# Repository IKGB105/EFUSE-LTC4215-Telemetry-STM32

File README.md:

# Hot-Swap eFuse Telemetry (LTC4215 + STM32F411CEU6)

Digital telemetry front-end for the [EFUSE-LTC4215-HotSwap](https://github.com/IKGB105/EFUSE-LTC4215-HotSwap)
board: adds a minimal STM32F411CEU6 system wired to the LTC4215's I²C/SMBus monitoring interface,
which the original design left completely unused. Same honest-engineering-logbook documentation
style as the rest of the series — every result marked calculated, simulated, or pending, no invented
placeholders.

- **Why:** the LTC4215 has an onboard ADC and I²C register map for current/voltage/fault monitoring
  that the original eFuse project never touched. This project closes that gap instead of starting an
  unrelated MCU exercise.
- **MCU:** STM32F411CEU6 (same part as the WeAct "Blackpill"), chosen for native USB-DFU flashing and
  headroom for future command parsing — not just familiarity.
- **Scope:** schematic + PCB layout only, same convention as every project in this series. Not
  physically built.

> ⚠️ **The LTC4215 is not PMBus-compliant.** It has its own proprietary I²C register map, not the
> standardized PMBus command set — described here as "digital power monitoring in the spirit of
> PMBus," not as a PMBus device, to avoid overstating the IC.

<table>
<tr>
<td><br><sub>KiCad — schematic</sub></td>
<td><br><sub>KiCad — PCB 3D render</sub></td>
<td><br><sub>KiCad — top copper routing</sub></td>
</tr>
</table>

## I²C integration with the LTC4215

The original eFuse board left every I²C-related pin (SCL, SDAI, SDAO, ADR0-2) no-connect. This
revision wires them per the datasheet:

- **SDAI + SDAO tied together** to form the bidirectional SDA line (the QFN exposes them separately
  only to allow an optoisolator on SDAO alone — not used here).
- **Address set to 19** (`ADR2`/`ADR0` to INTVCC, `ADR1` floating) — reproduced from the datasheet's
  own worked example (Figure 5), not an arbitrary value, since it's the only device on the bus.
- **Pull-ups referenced to INTVCC** (≈3.1 V typ, confirmed from the datasheet's electrical table to
  be close enough to 3.3 V logic that no level shifter is needed): 4.7 kΩ on SCL/SDA, 10 kΩ on ALERT.
- **-ALERT**, previously unused, now routed to the STM32 as an EXTI interrupt source.

## STM32 minimal system

Built from the real WeAct Blackpill reference schematic (`docs/reference/`), kept where it was
correct and corrected where it was not — see the report's pitfalls section for specifics:

- 3× VDD + 4× VSS (the UFQFPN48's exposed pad is a 4th, hidden VSS pin stacked on the visible one —
  verified directly from the symbol library file, not assumed).
- VCAP1 (2.2 µF, required for the F4's internal core regulator) and a VDDA/VREF+ LC filter.
- 25 MHz/9 pF crystal, 12 pF loading caps — **no RTC crystal/battery**, intentionally dropped (not
  needed for I²C telemetry).
- BOOT0 **and BOOT1** (shared with PB2 on the F401/F410/F411/F412 value line) pull-downs — confirmed
  against RM0383 §2.4 that BOOT1 is real on this part, not an F1-series leftover as first assumed.
- USB-C with a properly impedance-controlled D+/D− differential pair (90.2 Ω, computed from this
  board's real 2-layer stackup, not a generic assumption) and independent CC1/CC2 pull-downs.
- Single-stage **12 V → 3.3 V** LDO (LD1117S33TR) direct from the eFuse's +12 V rail — not the real
  Blackpill's two-stage USB-fed supply, since this board is never USB-powered.

## Firmware

I²C driver for the LTC4215 (`code/EFUSE_TELEMETRY/Core/{Inc,Src}/ltc4215.c,h`), on a STM32CubeMX
skeleton (I2C1 on PB6/PB7, USB\_OTG\_FS device-only with VBUS sensing disabled, USB\_DEVICE as
CDC/Virtual COM Port). Register map (CONTROL/ALERT/STATUS/FAULT/SENSE/SOURCE/ADIN, 00h-06h) and LSB
values taken straight from the datasheet's Tables 2-8, not re-derived. Main loop polls every 500 ms
and streams output current/voltage/fault flags over USB-CDC.

**Verified without any physical board, two ways:**
- Compiles clean against the real HAL — CMake + `arm-none-eabi-gcc`, 0 errors/warnings, 36020 B FLASH
  (6.87%), 9456 B RAM (7.21%).
- The register-to-physical-value math is checked on the **host** (plain `gcc`, no STM32 hardware) in
  [`code/test/ltc4215_regmap_test.c`](code/test/ltc4215_regmap_test.c) against synthetic bytes derived
  from the datasheet's LSB values — 11/11 checks pass.

Neither claims real I²C traffic with a physical LTC4215 — this board was never built.

## Repository structure

```
docs/         LaTeX report (efuse_telemetry_stm32.tex) + datasheet + WeAct reference schematic
kicad/        KiCad project — schematic + PCB, ERC/DRC clean
code/         STM32CubeMX project (CMake) + LTC4215 driver + host-side unit test
```

## Document

The full report (MCU selection rationale, I²C integration design, STM32 minimal-system design, PCB
layout decisions, and every pitfall found along the way — net-name collisions, hidden/stacked pins,
4-pad crystal footprints, differential pair impedance synthesis, a confirmed BOOT1 requirement) is in
[`docs/efuse_telemetry_stm32.pdf`](docs/efuse_telemetry_stm32.pdf) — compiled and committed. Source
is [`docs/efuse_telemetry_stm32.tex`](docs/efuse_telemetry_stm32.tex) if you want to edit or
recompile it yourself (`pdflatex`).

## PCB (KiCad)

In [`kicad/EFUSE_TELEMETRY/`](kicad/EFUSE_TELEMETRY/) — ERC and DRC both clean (the only remaining
DRC entries are inherent to the USB-C connector footprint itself: hole clearance to its own mounting
holes, and the four intentionally-No-Connect VBUS pads touching each other). Single sheet, organized
into labeled blocks (Controller, Protection, Power, Connectors, STM32 Microprocessor, MCU Support,
STM32 Decoupling, USB-C, 12V→3.3V) rather than hierarchical sheets — the board is small enough that
visual grouping is clearer.

## PDN analysis

<br>
<sub>padne — DC voltage distribution: 12V eFuse input (yellow/red) and the 3.3V/GND plane under the
STM32's 50mA load (purple), at most 148µV of drop.</sub>

DC voltage-drop check done with [`padne`](https://github.com/atx/padne) (built from source — needs
`boost` dev headers for its CGAL dependency): under the STM32's estimated 50 mA load, the 3.3 V/GND
plane shows at most **148 µV** of drop — the copper is far from the bottleneck at this current level.
`!padne` directives live as plain text in the schematic, not the PCB. Full write-up (including the
`REGULATOR`+`CURRENT` solver interaction that made the LDO need modeling as a plain ideal source
instead) in the report.

AC impedance-vs-frequency sweep (the actual question for a digital decoupling bank — DC drop is blind
to capacitors entirely) is planned with [KiPI](https://github.com/drewsum/KiPI) — installed and
loading the board, but the probe/sweep setup wasn't finished this session.

## License

MIT — see [LICENSE](LICENSE).

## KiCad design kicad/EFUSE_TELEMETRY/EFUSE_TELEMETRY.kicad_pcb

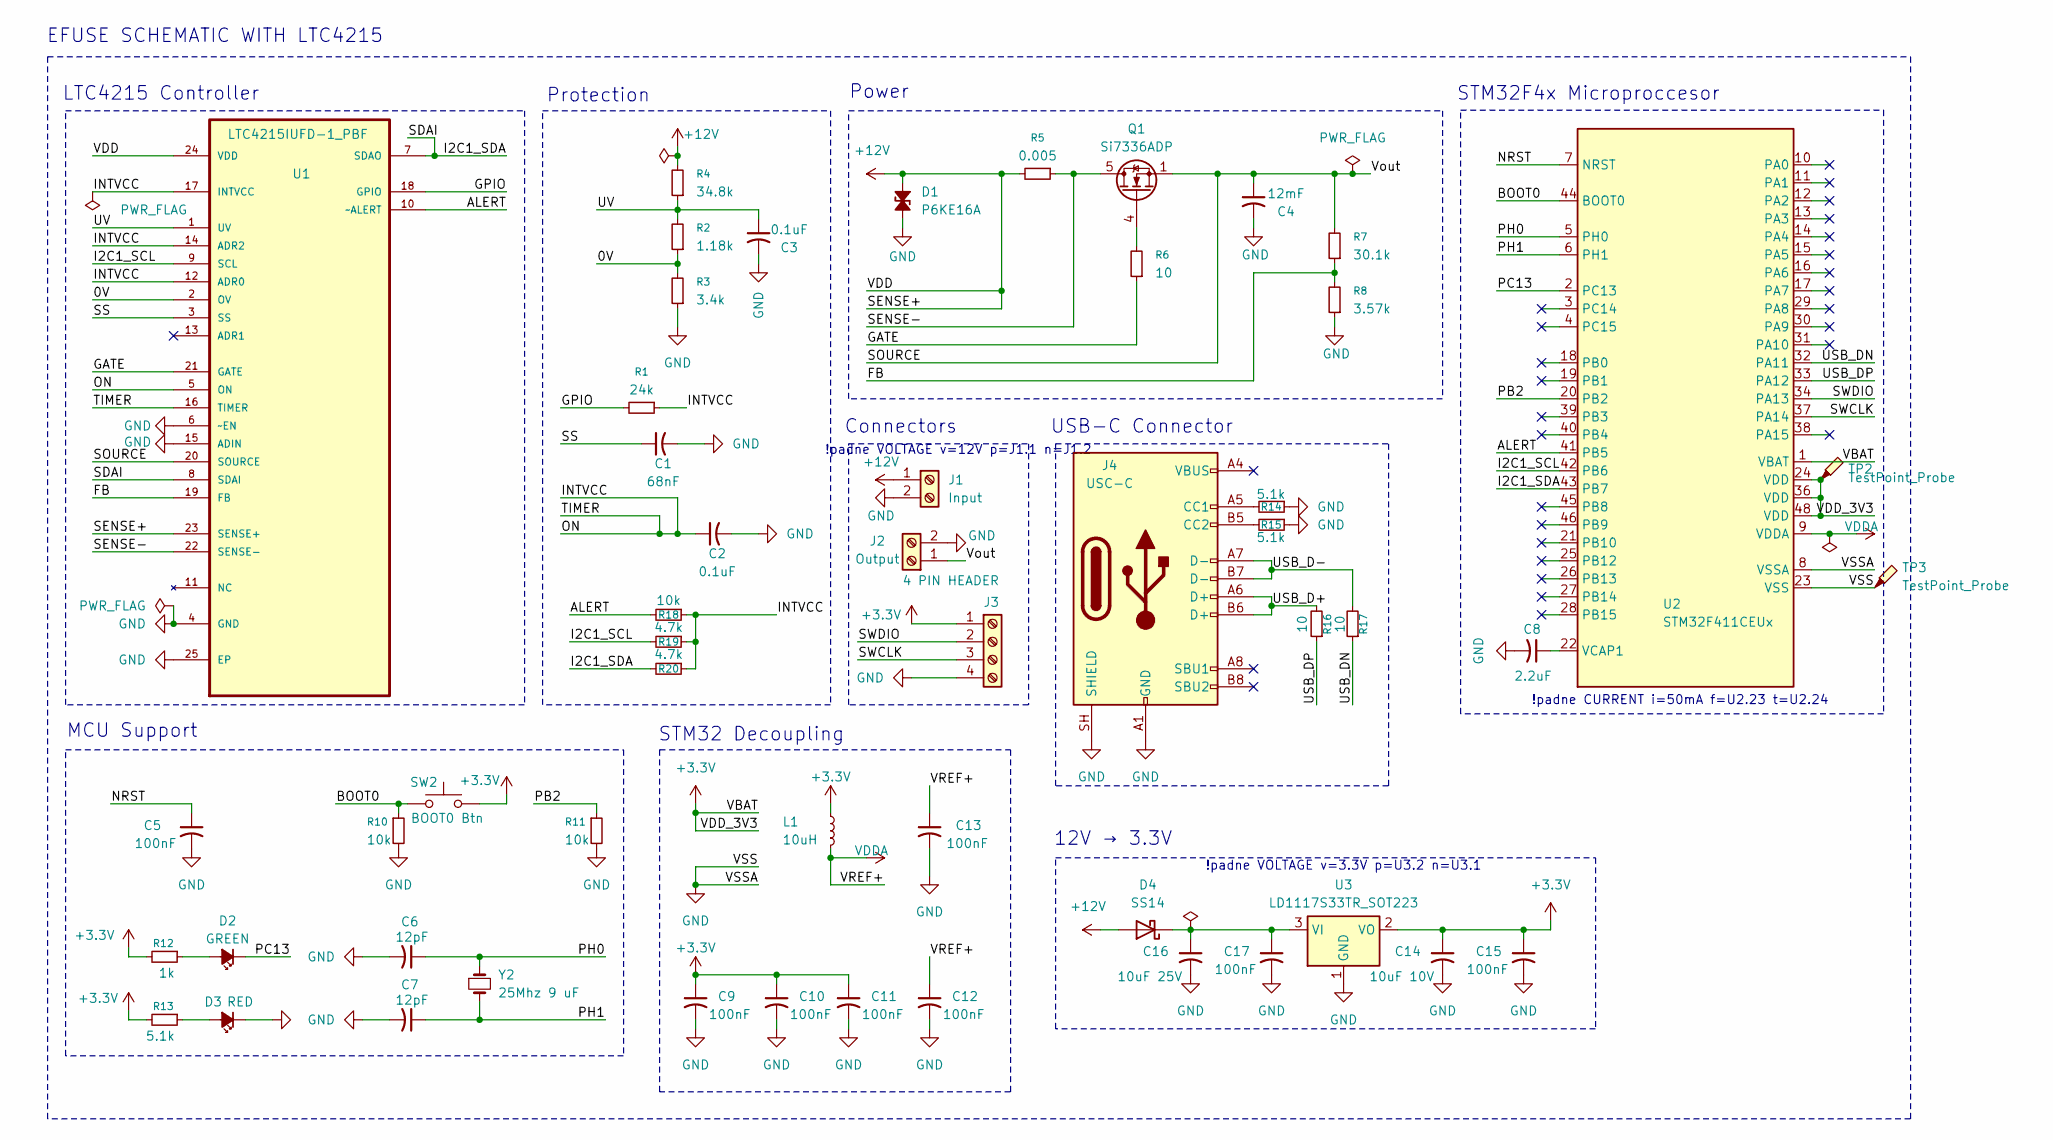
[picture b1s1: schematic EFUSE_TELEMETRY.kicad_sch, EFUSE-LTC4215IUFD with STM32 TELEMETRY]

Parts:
C1: 68nF; C_0805_2012Metric
C2, C3: 0.1uF; C_0805_2012Metric
C4: 12mF; CP_Radial_D16.0mm_P7.50mm
C5, C9, C10, C11, C12, C13, C15, C17: 100nF; C_0805_2012Metric
C6, C7: 12pF; C_0201_0603Metric
C8: 2.2uF; C_0805_2012Metric
C14: 10uF 10V; C_1206_3216Metric
C16: 10uF 25V; C_1206_3216Metric
D1: P6KE16A; D_DO-15_P10.16mm_Horizontal
D2: GREEN; LED_0603_1608Metric
D3: RED; LED_0603_1608Metric
D4: SS14; D_SMA
J1: Input; AMASS_XT60-M_1x02_P7.20mm_Vertical
J2: Output; AMASS_XT60-M_1x02_P7.20mm_Vertical
J3: 4 PIN HEADER; PinHeader_1x04_P2.54mm_Vertical
J4: USC-C; USB_C_Receptacle_GCT_USB4105-xx-A_16P_TopMnt_Horizontal
L1: 10uH; L_0805_2012Metric
Q1: Si7336ADP; PowerPAK_SO-8_Single
R1: 24k; R_0805_2012Metric
R2: 1.18k; R_0805_2012Metric
R3: 3.4k; R_0805_2012Metric
R4: 34.8k; R_0805_2012Metric
R5: 0.005; R_2512_6332Metric
R6, R16, R17: 10; R_0805_2012Metric
R7: 30.1k; R_0805_2012Metric
R8: 3.57k; R_0805_2012Metric
R10, R11, R18: 10k; R_0805_2012Metric
R12: 1k; R_0805_2012Metric
R13, R14, R15: 5.1k; R_0805_2012Metric
R19, R20: 4.7k; R_0805_2012Metric
SW2: BOOT0 Btn; SW_Tactile_SPST_NO_Straight_CK_PTS636Sx25SMTRLFS
TP2, TP3: TestPoint_Probe; TestPoint_Keystone_5000-5004_Miniature
U1: LTC4215IUFD-1_PBF; QFN50P400X500X80-25N; MPN LTC4215IUFD-2#TRPBF; DigiKey_Part_Number LTC4215IUFD-1#PBF-ND
U2: STM32F411CEUx; QFN-48-1EP_7x7mm_P0.5mm_EP5.6x5.6mm
U3: LD1117S33TR_SOT223; SOT-223-3_TabPin2
Y2: 25Mhz 9 uF; Crystal_SMD_3225-4Pin_3.2x2.5mm

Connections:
+3.3V: C9.1, C10.1, C11.1, C14.1, C15.1, J3.1, L1.1, R12.2, R13.2, SW2.2, TP2.1 (1_1), U2.1 (VBAT), U2.24 (VDD), U2.36 (VDD), U2.48 (VDD), U3.2 (VO)
+12V: D1.1 (A1), D4.2 (A), J1.1, R4.2, R5.2, U1.23 (SENSE+), U1.24 (VDD)
/0V: R2.1, R3.2, U1.2 (OV)
/ALERT: R18.2, U1.10 (~ALERT), U2.41 (PB5)
/BOOT0: R10.1, SW2.1, U2.44 (BOOT0)
/FB: R7.1, R8.2, U1.19 (FB)
/GATE: R6.1, U1.21 (GATE)
/GPIO: R1.2, U1.18 (GPIO)
/I2C1_SCL: R19.2, U1.9 (SCL), U2.42 (PB6)
/I2C1_SDA: R20.2, U1.7 (SDAO), U1.8 (SDAI), U2.43 (PB7)
/INTVCC: C2.1, R1.1, R18.1, R19.1, R20.1, U1.5 (ON), U1.12 (ADR0), U1.14 (ADR2), U1.16 (TIMER), U1.17 (INTVCC)
/NRST: C5.1, U2.7 (NRST)
/PB2: R11.1, U2.20 (PB2)
/PC13: D2.1 (K), U2.2 (PC13)
/PH0: C6.1, U2.5 (PH0), Y2.1
/PH1: C7.1, U2.6 (PH1), Y2.2
/SENSE-: Q1.5 (D), R5.1, U1.22 (SENSE-)
/SOURCE: C4.1, J2.1, Q1.1 (S), Q1.2 (S), Q1.3 (S), R7.2, U1.20 (SOURCE)
/SS: C1.1, U1.3 (SS)
/SWCLK: J3.3, U2.37 (PA14)
/SWDIO: J3.2, U2.34 (PA13)
/USB_D+: J4.A6 (D+), J4.B6 (D+), R16.2
/USB_D-: J4.A7 (D-), J4.B7 (D-), R17.2
/USB_DN: R17.1, U2.32 (PA11)
/USB_DP: R16.1, U2.33 (PA12)
/UV: C3.1, R2.2, R4.1, U1.1 (UV)
GND: C1.2, C2.2, C3.2, C4.2, C5.2, C6.2, C7.2, C8.2, C9.2, C10.2, C11.2, C12.2, C13.2, C14.2, C15.2, C16.2, C17.2, D1.2 (A2), D3.1 (K), J1.2, J2.2, J3.4, J4.A1 (GND), J4.A12 (GND), J4.B1 (GND), J4.B12 (GND), J4.SH (SHIELD), R3.1, R8.1, R10.2, R11.2, R14.1, R15.1, TP3.1 (1_1), U1.4 (GND), U1.6 (~EN), U1.15 (ADIN), U1.25 (EP), U2.8 (VSSA), U2.23 (VSS), U2.35 (VSS), U2.47 (VSS), U2.49 (VSS), U3.1 (GND)
unnamed: D2.2 (A), R12.1
unnamed: D3.2 (A), R13.1
unnamed: C16.1, C17.1, D4.1 (K), U3.3 (VI)
unnamed: J4.A5 (CC1), R14.2
unnamed: J4.B5 (CC2), R15.2
unnamed: Q1.4 (G), R6.2
unnamed: C8.1, U2.22 (VCAP1)
VDDA: C12.1, C13.1, L1.2, U2.9 (VDDA)

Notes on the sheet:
STM32F4x Microproccesor
Power
!padne CURRENT i=50mA f=U2.23 t=U2.24
MCU Support
STM32 Decoupling
!padne VOLTAGE v=3.3V p=U3.2 n=U3.1
Connectors
!padne VOLTAGE v=12V p=J1.1 n=J1.2
Protection
12V → 3.3V
LTC4215 Controller
EFUSE SCHEMATIC WITH LTC4215
USB-C Connector

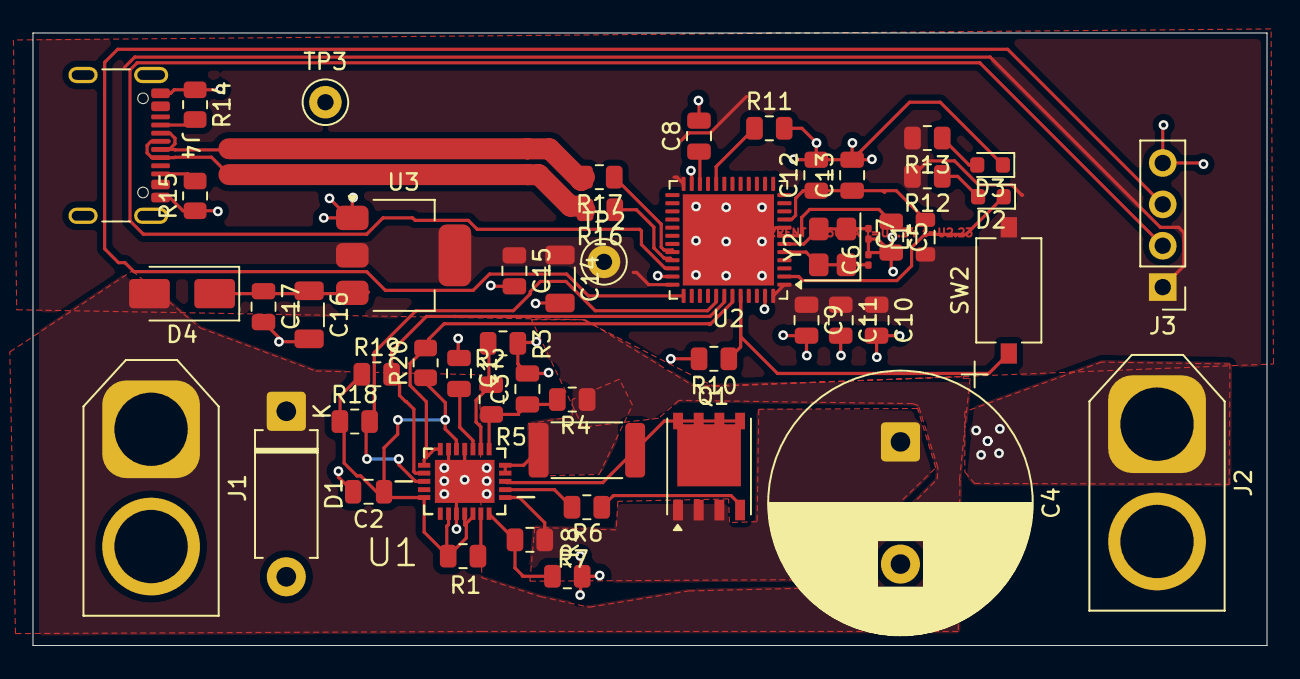
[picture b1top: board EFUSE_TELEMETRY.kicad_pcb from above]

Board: 2 copper layers, 75.8 x 37.6 mm, 53 parts (0 on the bottom side), 35 nets.

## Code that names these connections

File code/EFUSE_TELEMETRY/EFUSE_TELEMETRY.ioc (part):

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Mcu.Name=STM32F411C(C-E)Ux
Mcu.Package=UFQFPN48
Mcu.UserName=STM32F411CEUx
PA11.Mode=Device_Only
PA11.Signal=USB_OTG_FS_DM
PA12.Mode=Device_Only
PA12.Signal=USB_OTG_FS_DP
PB6.Mode=I2C
PB6.Signal=I2C1_SCL
PB7.Mode=I2C
PB7.Signal=I2C1_SDA
PH0\ -\ OSC_IN.Mode=HSE-External-Oscillator
PH0\ -\ OSC_IN.Signal=RCC_OSC_IN
PH1\ -\ OSC_OUT.Mode=HSE-External-Oscillator
PH1\ -\ OSC_OUT.Signal=RCC_OSC_OUT
RCC.HSE_VALUE=25000000
RCC.SYSCLKFreq_VALUE=96000000
RCC.SYSCLKSource=RCC_SYSCLKSOURCE_PLLCLK
board=custom
